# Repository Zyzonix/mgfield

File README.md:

# mgfield - Magnetic field measurement
This software has been developed with OCISLY-ds to measure magnetic fields with a Raspberry Pi.
For more details, please contact OCISLY-ds.

### Installation
**This software is designed to be run on a Raspberry Pi!**
First navigate to ```/opt/```:
```
cd /opt
```
Then install all required APT-packages:
```
sudo apt install mariadb-server git 
```
If required, also install ```phpmyadmin``` and ```libapache2-mod-php``` to make PHP work with Apache. After that clone the repository:
```
git clone https://github.com/Zyzonix/mgfield.git
cd mgfield/
```
Now all required software is downloaded.

To install the service type:
```
sudo cp services/mgfield.service /etc/systemd/system/
```

Enable the service with:
```
sudo systemctl enable mgfield.service
```

Install required python packages:
```
sudo apt install python3-psutil i2c-tools libgpiod-dev python3-libgpiod ./packages/* 
```
The usage of ```pip3``` depends on your system's configuration. Python packages on some systems like Debian are managed via ```apt```.
```
sudo pip3 install mysql-connector
```
Install additional python packages for physical sensor:
```
pip3 install --upgrade RPi.GPIO adafruit-blinka
pip3 install adafruit-circuitpython-ads1x15
```
Create config directory and move config file:
```
sudo mkdir -p /home/root/.config/
cp config.json /home/root/.config/
```
And finally create the logfile directory:
```
sudo mkdir -p /var/log/mgfield/
```

### Execution
Directly over the console (the programm will interrupt when the window will be closed)
```
python3 main.py
```
Or via the system service
```
sudo systemctl start mgfield.service
```
To view the current status use:
```
sudo systemctl status mgfield.service
```
To view the log/consoleout in realtime use:
```
sudo journalctl -u MGField.service
```

### Settings
The software can be configured through the config-file named ```config.json```. 

- Thereby that collecting all values from each measurement (x, y, z and out) might be to heavy for a Raspberry Pi, there's a switch called ```storeAllRawData``` in the config that can be used to en-/disable the storing of this data.
- Also a specific path to the temperature sensor must be provided config. If the device can't be opened the return value of the sensor will be 0.00. The right format of the sensor's path is for example: ```/sys/bus/w1/devices/28-01204b515089/w1_slave```

### SQL Value Meanings
**Each table contains two rows:**
Value Name | Meaning/Use type
---|---
```time_utc```|Timestamp of value in **UTC**
```time_local```|Timestamp of value in local time (```Europe/Berlin```/ ```+02:00```)

**All other values are table-specific:**
Table | Value Name | Meaning/Use type
---|---|---
```mgfield```|```x_value```|X-Value per measurement
```mgfield```|```y_value```|Y-Value per measurement
```mgfield```|```z_value```|Z-Value per measurement
```mgfield```|```out_value```|OUT-Value per measurement
```mgfield```|```measurement_duration```|Time delta of the single measurement
```netstats```|```hostname```|Local hostname from ```/etc/hosts```
```netstats```|```local_ip```|Local IP
```netstats```|```packets_sent```|Packets sent
```netstats```|```packets_recv```|Packets received
```netstats```|```errin```|Incoming packets with errors
```netstats```|```errout```|Outgoing packets with errors
```netstats```|```dropin```|Dropped incoming packets
```netstats```|```dropout```|Dropped outgoing packets
```netstats```|```target1```|Any target configured to be pinged
```netstats```|```target2```|Any target configured to be pinged
```netstats```|```target3```|Any target configured to be pinged
```sysstats```|```cpu_speed```|CPU Speed in MHz
```sysstats```|```cpu_usage```|Current CPU usage in %
```sysstats```|```cpu_ctx_switches```| CPU CTX Switches
```sysstats```|```cpu_interrupts```| CPU interrupts since last boot
```sysstats```|```cpu_soft_interrupts```| CPU soft interrupts since last boot
```sysstats```|```ram_total```|Total RAM in MB
```sysstats```|```ram_free```|Free RAM in MB
```sysstats```|```ram_used```|Used RAM in MB
```sysstats```|```ram_cached```|Cached RAM in MB
```sysstats```|```ram_free_wcache_perc```|Free RAM in % with cache
```sysstats```|```ram_free_wocache_perc```|Free RAM in % without cache
```sysstats```|```cpu_thermal```|Raspberry Pi's CPU Temperature
```sysstats```|```uptime```|Uptime since last reboot in seconds
```temperature```|```temperature_value```|Current temperature in °C

-----
This software was earlier named ```MGFieldPy```.

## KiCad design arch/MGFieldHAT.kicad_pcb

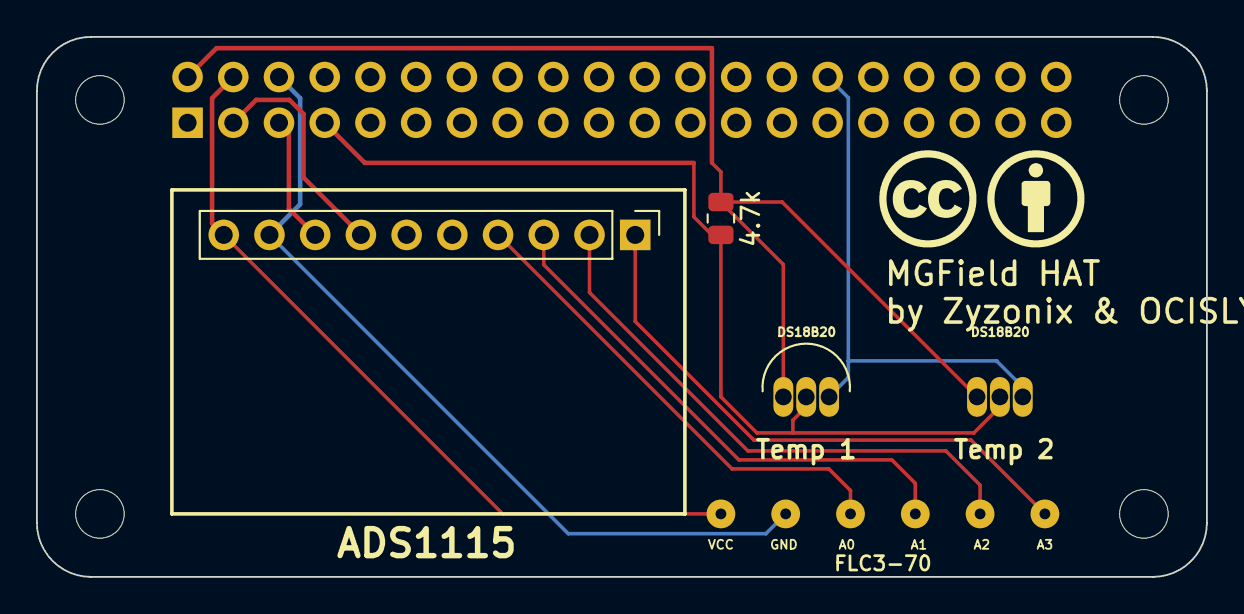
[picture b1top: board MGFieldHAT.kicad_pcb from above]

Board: 2 copper layers, 65.0 x 30.0 mm, 10 parts (1 on the bottom side), 6 nets.

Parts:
4.7k: Resistor 4.7k; R_0805_2012Metric
ADS1115: ADS1115; PinHeader_1x10_P2.54mm_Vertical
DS18B20, DS18B20#2: TO-92-TO92127P495H2044-3
FLC3-70: SolderWire-0.1sqmm_1x06_P3.6mm_D0.4mm_OD1mm
Header: GPIO; PinSocket_2x20_P2.54mm_Vertical
MH1, MH2, MH3, MH4: MountingHole_2.7mm_M2.5

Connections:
+3V3: Header.1, Header.17
+5V: 4.7k.1, ADS1115.10, DS18B20.1, DS18B20#2.1, FLC3-70.1, Header.2, Header.4
/GPIO2/SDA1: ADS1115.7, Header.3
/GPIO3/SCL1: ADS1115.8, Header.5
/GPIO4/GPCLK0: 4.7k.2, DS18B20.2, DS18B20#2.2, Header.7
GND: ADS1115.9, DS18B20.3, DS18B20#2.3, FLC3-70.2, Header.6, Header.9, Header.14, Header.20, Header.25, Header.30, Header.34, Header.39

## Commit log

2021-04-26 uploaded version 0.1
2021-04-26 updated the README
2021-04-26 uploaded the service file
2021-05-24 fixed temperature str-float issue
2021-05-24 inserted errorprint in MGFieldCore
2021-05-24 fixed configimport mistake
2021-06-04 inserted some try-except
2021-06-29 Commends on dataHandler.py
2021-07-03 Update I2c input
2021-07-03 Update xlsxHandler.py
    Add MGField Value 2
2021-07-03 inserted new descriptions (comments)
2021-07-03 fixed handleInputMethod-fuction
2021-07-03 inserted new descriptions (comments) and inserted second input-method
2021-07-05 refreshed the README
2021-07-05 inserted new console output
2021-07-06 Fixed an issue
2021-07-06 Fixed error ads
2021-07-09 Reichelt Magazin Text hinzugefügt
2021-10-04 removed unnecessary files for v2.0
2021-10-04 uploaded software blueprint | v2.0
2021-10-04 uploaded repo-stuff | v2.0
2021-10-28 Fixed issue with Memory usage recording
    For the project it is necessary to knew the available Memory in %. Not the Ram utilisation in %
2021-10-28 Updated description for the first row
2022-01-24 uploaded version v.1.1 (final)
    New features:
    - Excel/CSV switch
    - Sensor number switch
    - Venv (Virtual Sensor) can now be run on every device that suppots Python3
    - Added more details to console output (milliseconds)
    - Added some more try-except functions
2022-01-24 uploaded version v.1.11
2022-01-29 Update on OneWire Sensor ID
2023-09-18 Updated MGFieldPy
2023-09-18 Fixed input error
2023-09-18 Fixed calculating error
2023-09-18 Cleaned up
2023-09-18 Added debug line
2023-09-18 Added debug line for sensor
2023-09-19 Updated system statistics collector
2023-09-19 Fixed CSV head row description
2023-09-19 Fixed cached memory information
2023-09-28 Create devcontainer.json
    Copilot
2024-03-29 created new systemd-service
2024-03-29 saved old release for backup purposes in subdirectory
2024-03-29 removed url
2024-03-30 added .gitignore
2024-03-31 created sql-DB template
2024-03-31 updated sql-DB template
2024-03-31 updated formats in mysql-DB template and fixed typos
2024-04-01 added config file for new version
2024-04-01 updated .gitignore
2024-04-01 removed old MGFieldPy version
2024-04-01 uploaded new version of MGFieldPy
2024-04-02 added SQL Value Meanings to README
2024-04-02 changed saving mechanism of temperature and sysstats data
2024-04-02 updated logging when writing to SQL
2024-04-04 implemented UTC as default time
2024-04-04 updated the SQL template for UTC times
2024-04-16 updated typo in MGFieldPy.service
2024-04-16 fixed typo in MGFieldPy.service
2024-04-16 added missing ExecStart parameter in MGFieldPy.service
2024-04-28 updated SQL template for v2.1
2024-04-28 updated main script to v2.1
2024-04-28 updated config to v2.1
2024-05-01 uploaded debian python-mysql.connector package for
2024-05-01 updated mysqlHandler to v2.1
2024-05-01 renamed service
2024-05-05 fixed naming and issue when using physical sensor
2024-05-05 fixed console output of physicalSensor requests
2024-05-05 updated gitignore
2024-05-06 README.md aktualisiert für Board
2024-05-06 README.md aktualisieren
2024-05-22 renamed table allmeasurements.raw to rawmeasurements (#6)
2024-05-22 added out calibration value (#5)
2024-08-06 changed default user in system service (#15)
2024-08-06 added delay functionality (#11)
2024-08-08 uploaded python3-ping3-package
2024-08-08 renamed service file
2024-08-08 removed old service file
2024-08-08 updated system statistics (#12)
2024-08-08 added monitoring of threading (#14)
2024-08-08 moved config to JSON (#15)
2024-08-08 renamed project
2024-08-08 fixed typo
2024-08-08 updated naming
2024-08-09 removed any calculation while measuring
2024-08-09 fixed removal mistake
2024-08-09 delayed automatic start via systemd to allow mySQL to start correctly
2024-08-09 fixed output of service
2024-08-09 updated README to current database structure
2024-08-11 added mySQL template for calculation addon
2024-08-13 added indicator for avg-calculation addon
2024-08-13 updated sql templates
2024-08-13 completely removed any calculation
2024-12-24 Created Analyse tool
2025-01-08 added second station
2025-01-08 file name, initial commit
2025-01-08 added csv output of kp index
2025-01-09 Create intermagnet-wng.py
    added intermagnet wrapper for wng
2025-01-09 Update intermagnet-wng.py
    added copyright
2025-01-12 Plotting locations and multiple sites.
2025-01-12 example_locationoutput
2025-01-13 added auto selected stations
2025-01-13 updated to wished citation format by author
2025-01-29 created MGField Hat
2025-01-29 Added Photo for the MGField Hat
2025-01-29 Added MGField Header picture
2025-01-30 added kicad file
2025-02-09 added uptime monitoring (#19)
2025-04-22 added script for remote calculation
2025-04-24 added additional notes
